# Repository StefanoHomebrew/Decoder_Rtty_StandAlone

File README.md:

Un semplice decodificatore "stand alone" per RTTY & CW (prossimo) con Arduino Nano -display TFT a colori - scelta velocià a 45/50 Baud e I.C. NE567

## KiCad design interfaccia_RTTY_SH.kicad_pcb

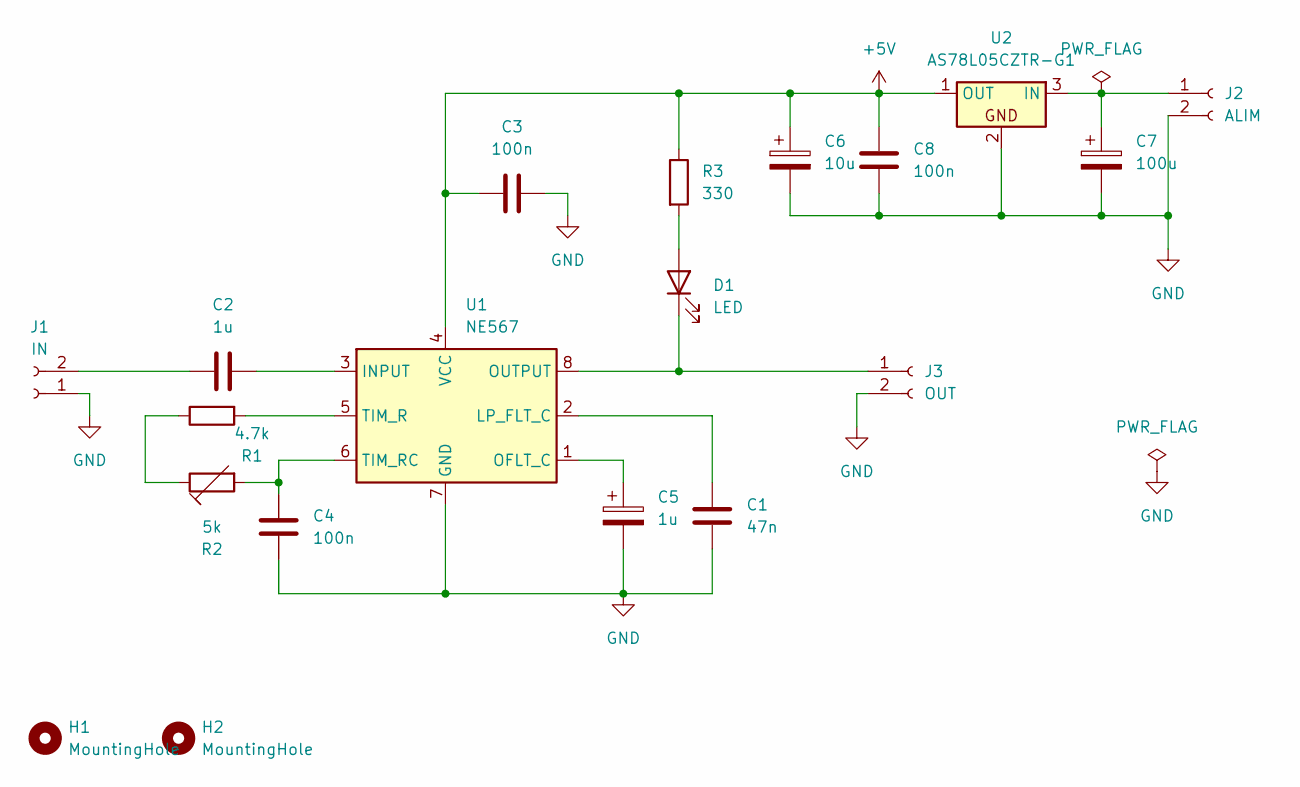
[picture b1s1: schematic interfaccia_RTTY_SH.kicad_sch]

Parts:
C1: 47n; C_Disc_D4.3mm_W1.9mm_P5.00mm
C2: 1u; C_Disc_D4.3mm_W1.9mm_P5.00mm
C3, C4, C8: 100n; C_Disc_D4.3mm_W1.9mm_P5.00mm
C5: 1u; CP_Radial_D8.0mm_P3.50mm
C6: 10u; CP_Radial_D8.0mm_P3.50mm
C7: 100u; CP_Radial_D8.0mm_P3.50mm
D1: LED; LED_D5.0mm_Clear
H1, H2: MountingHole; MountingHole_2.2mm_M2_Pad
J1: IN; PinHeader_1x02_P2.54mm_Vertical
J2: ALIM; PinHeader_1x02_P2.54mm_Vertical
J3: OUT; PinHeader_1x02_P2.54mm_Vertical
R1: 4.7k; R_Axial_DIN0207_L6.3mm_D2.5mm_P10.16mm_Horizontal
R2: 5k; Potentiometer_Runtron_RM-063_Horizontal
R3: 330; R_Axial_DIN0207_L6.3mm_D2.5mm_P10.16mm_Horizontal
U1: NE567; DIP-8_W7.62mm_Socket_LongPads
U2: AS78L05CZTR-G1; TO-92_Inline_Wide

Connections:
+5V: C3.1, C6.1, C8.1, R3.1, U1.4 (VCC), U2.1 (OUT)
GND: C1.2, C3.2, C4.1, C5.2, C6.2, C7.2, C8.2, J1.1, J2.2, J3.2, U1.7 (GND), U2.2
unnamed: D1.2 (A), R3.2
unnamed: D1.1 (K), J3.1, U1.8 (OUTPUT)
unnamed: C2.1, J1.2
unnamed: C7.1, J2.1, U2.3 (IN)
unnamed: R1.1, R2.1
unnamed: C2.2, U1.3 (INPUT)
unnamed: C1.1, U1.2 (LP_FLT_C)
unnamed: C5.1, U1.1 (OFLT_C)
unnamed: R1.2, U1.5 (TIM_R)
unnamed: C4.2, R2.2, U1.6 (TIM_RC)

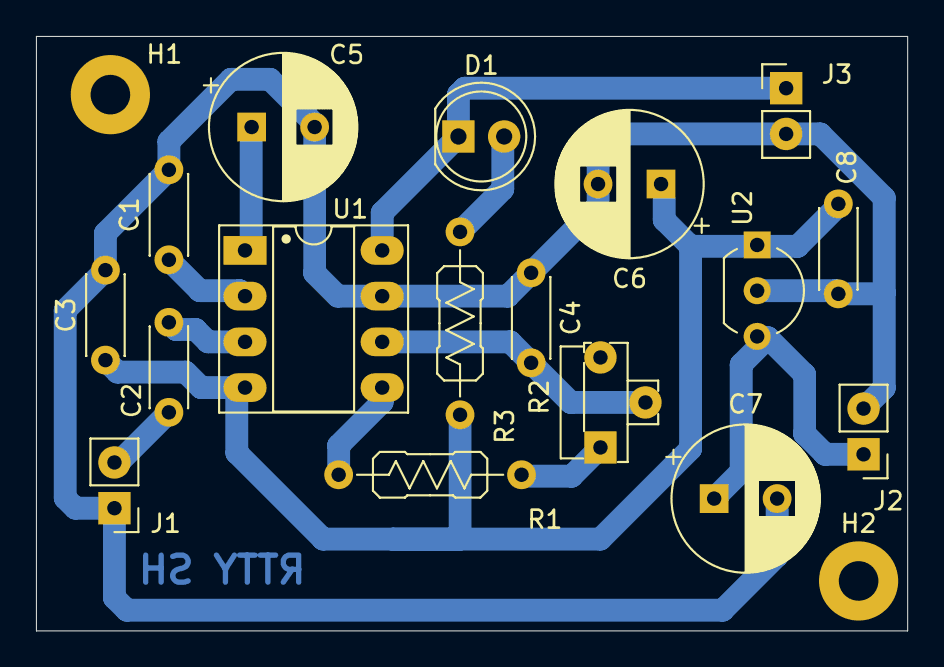
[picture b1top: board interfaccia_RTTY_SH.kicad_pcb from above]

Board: 2 copper layers, 48.4 x 33.0 mm, 19 parts (0 on the bottom side), 12 nets.

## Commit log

2025-08-15 Kicad 9.0 Files
2025-08-15 Arduino Nano Module schema
2025-08-15 SCHEMA .jpg
2025-08-15 PCB ARDUINO NANO -PDF-
2025-08-15 Arduino_Nano_.Hex_FIle_First_Release
